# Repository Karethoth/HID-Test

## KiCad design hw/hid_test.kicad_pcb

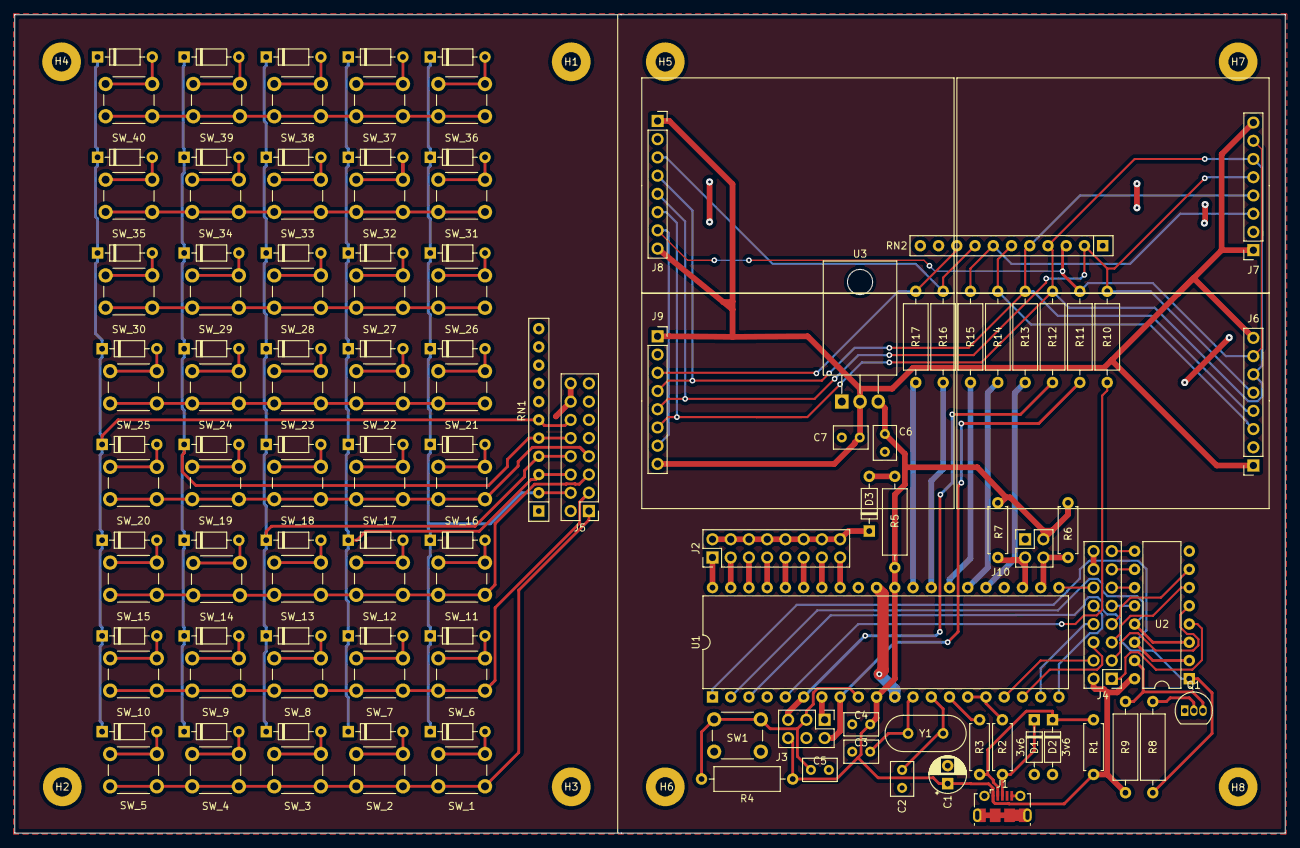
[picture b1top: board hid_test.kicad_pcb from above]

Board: 2 copper layers, 177.0 x 114.0 mm, 133 parts (0 on the bottom side), 110 nets.

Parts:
C1: 4u7; CP_Radial_D5.0mm_P2.50mm
C2, C3: 15p; C_Rect_L4.6mm_W3.0mm_P2.50mm_MKS02_FKP02
C4, C5, C6: 100n; C_Rect_L4.6mm_W3.0mm_P2.50mm_MKS02_FKP02
C7: 10μ; C_Rect_L4.6mm_W3.0mm_P2.50mm_MKS02_FKP02
D1, D2: 3v6; D_DO-35_SOD27_P7.62mm_Horizontal
D3: D; D_DO-35_SOD27_P7.62mm_Horizontal
D4, D5, D6, D7, D8, D9, D10, D11, D12, D13, D14, D15, D16, D17, D18, D19, D20, D21, D22, D23, D24, D25, D26, D27, D28, D29, D30, D31, D32, D33, D34, D35, D36, D37, D38, D39, D40, D41, D42, D43: 1N4153; D_DO-35_SOD27_P7.62mm_Horizontal_No_Ref
H1, H2, H3, H4, H5, H6, H7, H8: Hole; MountingHole_2.7mm_M2.5_Pad
J1: USB_B_Micro; USB_Micro-B_Molex-105017-0001
J2, J4: 2x8 Connector; PinHeader_2x08_P2.54mm_Vertical
J3: ISP; PinHeader_2x03_P2.54mm_Vertical
J5: 2x8; PinHeader_2x08_P2.54mm_Vertical
J6, J7, J8, J9: ILI9163; ILI9163_PinSocket_1x08_P2.54mm_Vertical
J10: TWI; PinSocket_2x02_P2.54mm_Vertical
Q1: 2N3904; TO-92_Inline
R1: 1k5; R_Axial_DIN0207_L6.3mm_D2.5mm_P7.62mm_Horizontal
R2, R3: 100; R_Axial_DIN0207_L6.3mm_D2.5mm_P7.62mm_Horizontal
R4, R8: 10k; R_Axial_DIN0309_L9.0mm_D3.2mm_P12.70mm_Horizontal
R5: 1k; R_Axial_DIN0309_L9.0mm_D3.2mm_P12.70mm_Horizontal
R6, R7: 4.7k; R_Axial_DIN0207_L6.3mm_D2.5mm_P7.62mm_Horizontal
R9: 5k; R_Axial_DIN0309_L9.0mm_D3.2mm_P12.70mm_Horizontal
R10, R11, R12, R13, R14, R15, R16, R17: 500; R_Axial_DIN0309_L9.0mm_D3.2mm_P12.70mm_Horizontal
RN1: 4.7k; R_Array_SIP11
RN2: 1k; R_Array_SIP11
SW1: SW_Push; SW_PUSH_6mm
SW_1, SW_2, SW_3, SW_4, SW_5, SW_6, SW_7, SW_8, SW_9, SW_10, SW_11, SW_12, SW_13, SW_14, SW_15, SW_16, SW_17, SW_18, SW_19, SW_20, SW_21, SW_22, SW_23, SW_24, SW_25, SW_26, SW_27, SW_28, SW_29, SW_30, SW_31, SW_32, SW_33, SW_34, SW_35, SW_36, SW_37, SW_38, SW_39, SW_40: Btn; SW_PUSH_6mm
U1: ATmega644-20PU; DIP-40_W15.24mm
U2: CD4555BE; DIP-16_W7.62mm
U3: LD1117S33TR; TO-220-3_Horizontal_TabDown
Y1: 20MHz; Crystal_HC49-U_Vertical

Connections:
+3V3: C7.2, J6.1, J6.8, J7.1, J7.8, J8.1, J8.8, J9.1, J9.8, U3.2
+5V: C1.1, C4.1, C6.2, J1.1, J3.6, J4.2, J10.3, R1.1, R4.1, R5.1, R6.1, R7.1, R9.1, U1.10, U1.30, U2.16, U3.3
DISPLAY_SEL_1: R14.1, U1.26
DISPLAY_SEL_1_3v3: J6.3, R14.2, RN2.6
DISPLAY_SEL_2: R15.1, U1.27
DISPLAY_SEL_2_3v3: J7.3, R15.2, RN2.7
DISPLAY_SEL_3: R16.1, U1.28
DISPLAY_SEL_3_3v3: J8.3, R16.2, RN2.8
DISPLAY_SEL_4: R17.1, U1.29
DISPLAY_SEL_4_3v3: J9.3, R17.2, RN2.9
DISPLAY_~RST~: R13.1, U1.25
DISPLAY_~RST~_3v3: J6.4, J7.4, J8.4, J9.4, R13.2, RN2.5
GND: C1.2, C2.2, C3.2, C4.2, C5.2, C6.1, C7.1, D1.2, D2.2, H1.1, H2.1, H3.1, H4.1, H5.1, H6.1, H7.1, H8.1, J1.5, J1.6, J3.4, J4.14, J4.16, J5.14, J5.16, J6.2, J7.2, J8.2, J9.2, J10.1, Q1.1, RN1.1, RN2.1, SW1.1, U1.11, U1.31, U2.8, U3.1
ISP_~RST: C5.1, J3.3, R4.2, SW1.2, U1.9
Marix_Row_5: SW_21.1, SW_22.1, SW_23.1, SW_24.1, SW_25.1
MatrixBoard_Row_1: J5.1, SW_1.1, SW_2.1, SW_3.1, SW_4.1, SW_5.1
MatrixBoard_Row_2: J5.3, SW_6.1, SW_7.1, SW_8.1, SW_9.1, SW_10.1
MatrixBoard_Row_3: J5.5, SW_11.1, SW_12.1, SW_13.1, SW_14.1, SW_15.1
MatrixBoard_Row_4: J5.7, SW_16.1, SW_17.1, SW_18.1, SW_19.1, SW_20.1
Matrix_0b: U1.1, U2.2, U2.14
Matrix_1b: U1.2, U2.3, U2.13
Matrix_2b: R8.1, U1.3, U2.1
Matrix_Row_6: SW_26.1, SW_27.1, SW_28.1, SW_29.1, SW_30.1
Matrix_Row_7: SW_31.1, SW_32.1, SW_33.1, SW_34.1, SW_35.1
Matrix_Row_8: SW_36.1, SW_37.1, SW_38.1, SW_39.1, SW_40.1
Matrix_press_A: J4.4, U1.17
Matrix_press_B: J4.6, U1.18
Matrix_press_C: J4.8, U1.19
Matrix_press_D: J4.10, U1.20
Matrix_press_E: J4.12, U1.21
unnamed: C2.1, U1.13, Y1.1
unnamed: C3.1, U1.12, Y1.2
unnamed: D1.1, J1.3, R2.2
unnamed: D2.1, J1.2, R1.2, R3.2
unnamed: D3.1, J2.2, J2.4, J2.6, J2.8, J2.10, J2.12, J2.14, J2.16
unnamed: D3.2, R5.2
unnamed: D4.2, SW_1.2
unnamed: D5.2, SW_6.2
unnamed: D6.2, SW_11.2
unnamed: D7.2, SW_16.2
unnamed: D8.2, SW_2.2
unnamed: D9.2, SW_7.2
unnamed: D10.2, SW_12.2
unnamed: D11.2, SW_17.2
unnamed: D12.2, SW_3.2
unnamed: D13.2, SW_8.2
unnamed: D14.2, SW_13.2
unnamed: D15.2, SW_18.2
unnamed: D16.2, SW_4.2
unnamed: D17.2, SW_9.2
unnamed: D18.2, SW_14.2
unnamed: D19.2, SW_19.2
unnamed: D20.2, SW_5.2
unnamed: D21.2, SW_10.2
unnamed: D22.2, SW_15.2
unnamed: D23.2, SW_20.2
unnamed: D24.2, SW_21.2
unnamed: D25.2, SW_26.2
unnamed: D26.2, SW_31.2
unnamed: D27.2, SW_36.2
unnamed: D28.2, SW_22.2
unnamed: D29.2, SW_27.2
unnamed: D30.2, SW_32.2
unnamed: D31.2, SW_37.2
unnamed: D32.2, SW_23.2
unnamed: D33.2, SW_28.2
unnamed: D34.2, SW_33.2
unnamed: D35.2, SW_38.2
unnamed: D36.2, SW_24.2
unnamed: D37.2, SW_29.2
unnamed: D38.2, SW_34.2
unnamed: D39.2, SW_39.2
unnamed: D40.2, SW_25.2
unnamed: D41.2, SW_30.2
unnamed: D42.2, SW_35.2
unnamed: D43.2, SW_40.2
unnamed: J2.1, U1.40
unnamed: J2.3, U1.39
unnamed: J2.5, U1.38
unnamed: J2.7, U1.37
unnamed: J2.9, U1.36
unnamed: J2.11, U1.35
unnamed: J2.13, U1.34
unnamed: J2.15, U1.33
unnamed: J4.1, U2.4
unnamed: J4.3, U2.5
unnamed: J4.5, U2.6
unnamed: J4.7, U2.7
unnamed: J4.9, U2.12
unnamed: J4.11, U2.11
unnamed: J4.13, U2.10
unnamed: J4.15, U2.9
unnamed: Q1.2, R8.2
unnamed: Q1.3, R9.2, U2.15
SPI_MISO: J3.1, U1.7
SPI_MOSI: J3.5, R12.1, U1.6
SPI_SCK: J3.2, R11.1, U1.8
SPI_SCK_3v3: J6.7, J7.7, J8.7, J9.7, R11.2, RN2.3
SPI_SDA_3v3: J6.6, J7.6, J8.6, J9.6, R12.2, RN2.4
SPI_~SS: R10.1, U1.5
SPI_~SS~_3v3: J6.5, J7.5, J8.5, J9.5, R10.2, RN2.2
Switch_Matrix_A: D4.1, D5.1, D6.1, D7.1, D24.1, D25.1, D26.1, D27.1, J5.4, RN1.2
Switch_Matrix_B: D8.1, D9.1, D10.1, D11.1, D28.1, D29.1, D30.1, D31.1, J5.6, RN1.3
Switch_Matrix_C: D12.1, D13.1, D14.1, D15.1, D32.1, D33.1, D34.1, D35.1, J5.8, RN1.4
Switch_Matrix_D: D16.1, D17.1, D18.1, D19.1, D36.1, D37.1, D38.1, D39.1, J5.10, RN1.5
Switch_Matrix_E: D20.1, D21.1, D22.1, D23.1, D40.1, D41.1, D42.1, D43.1, J5.12, RN1.6
TWI_SCL: J10.2, R7.2, U1.23
TWI_SDA: J10.4, R6.2, U1.22
USB_D+: R2.1, U1.15, U1.16
USB_D-: R3.1, U1.14

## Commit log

2020-03-02 Initial schematic
    - Basic USB-circuitry
    - Reset & XTAL
2020-03-02 Added CD4555BE
2020-03-02 Pin layout update
2020-03-02 3 to 8 block
2020-03-02 ADC-port
2020-03-02 Added the programming connector
2020-03-02 Key matrix
2020-03-02 Added ILI9163
2020-03-02 Added SN74HC148N
2020-03-02 Split sheet
2020-03-05 Fix for CD4555BE and little changes
2020-03-05 Switch matrix updated, SPI bus
2020-03-09 4 x ILI9163 & some changes
2020-03-09 Fix node name
2020-03-09 Initial software commit
2020-03-10 Keypad testing
2020-03-10 Reading keypad works
2020-03-10 Layout update
2020-03-11 Pull-down resistors work well enough
2020-03-11 No need for internal pull-ups
2020-03-11 Layout update for USB
2020-03-11 Created circuit PDFs & added V-USB
2020-03-11 Just the usbdrv
2020-03-12 Switched in two resistor networks
2020-03-12 The device gets noticed over USB now
2020-03-12 Update the circuit diagram
2020-03-13 Component footprints and ratsnest
2020-03-13 Add the lib table
2020-03-13 PCB component placing before routing
2020-03-13 Little adjustments and basic design limits
2020-03-14 Can't have too many vias, right?
2020-03-14 Little fixes
2020-03-14 Fix GND in couple places. Added drill files
2020-03-15 Little adjustments and added mounting holes
2020-03-23 "Reset" & "clear" commands work over USB
2020-03-23 Required files added
2020-03-24 Reorganizing code. Display class added
2020-03-24 Fixed coordinate problems for rotated displays
